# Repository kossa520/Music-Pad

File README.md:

# Music Pad Images:

## Preview:

## PCB Schemat:

## Case Schemat:

#  Project Requirements

## File List
* **PCB Design:**
  * `Music Pad.kicad_pcb`
  * `Music Pad.kicad_sch`
  * `Music Pad.kicad_pro`
* **Case Design:**
  * `Bottom.step`
  * `Top.step`
* **Keyboard Layout Styles:**
  * `keyboard-layout.json`
  * `plate-2026-02-05T17_30_58.558Z.dxf`
* **Programs:**
  * `code.py`
  * `libraries`

---

## Part List
| Quantity | Item | Notes |
| :--- | :--- | :--- |
| 1 | 3D Printed Case | Includes Bottom and Top files |
| 4 | M3x5mx4mm Heatset Inserts | |
| 4 | M3x16mm Screws | |
| 1 | 0.91 inch OLED Display | 4-pin version |
| 3 | DSA Keycaps | |
| 1 | Seeed XIAO RP2040 | |
| 3 | MX-Style Switches | |
| 1 | EC11 Rotary Encoder | |

## Setup Guide

### 1. Install CircuitPython

Download CircuitPython for XIAO RP2040 from [circuitpython.org](https://circuitpython.org/board/seeeduino_xiao_rp2040/)
Double-press the reset button on your XIAO RP2040 to enter bootloader mode
A drive named RPI-RP2 will appear
Copy the downloaded .uf2 file to this drive
The board will restart and appear as CIRCUITPY

### 2. Install Required Libraries

Download the CircuitPython libraries
Copy these folders/files to the lib folder on your CIRCUITPY drive:

adafruit_hid/
adafruit_display_text/
adafruit_framebuf.mpy
adafruit_ssd1306.mpy

### 3. Upload Firmware

Copy the music_pad_firmware.py firmware to the root of your CIRCUITPY drive
The board will automatically restart
You should see "Music Pad" and "Loading..." on the OLED display

## 4. Install Spotify Sender

Download Spotify Sender from programs folder
Go to https://developer.spotify.com/dashboard and click create app
Insert whatever name and description you want and in redirect URLs paste this: http://127.0.0.1:8888/callback
Click Web API and check the terms box then save
You will get your Client ID and client Secret copy those to the Spotify sender porgram you have downloaded 
Run the Spotify sender it should open chrome tab authorize it.

## Problems

If you have access denied problem with spotify sender try closing all apps that are using serial port with your RP2040 (for example MU Editor)

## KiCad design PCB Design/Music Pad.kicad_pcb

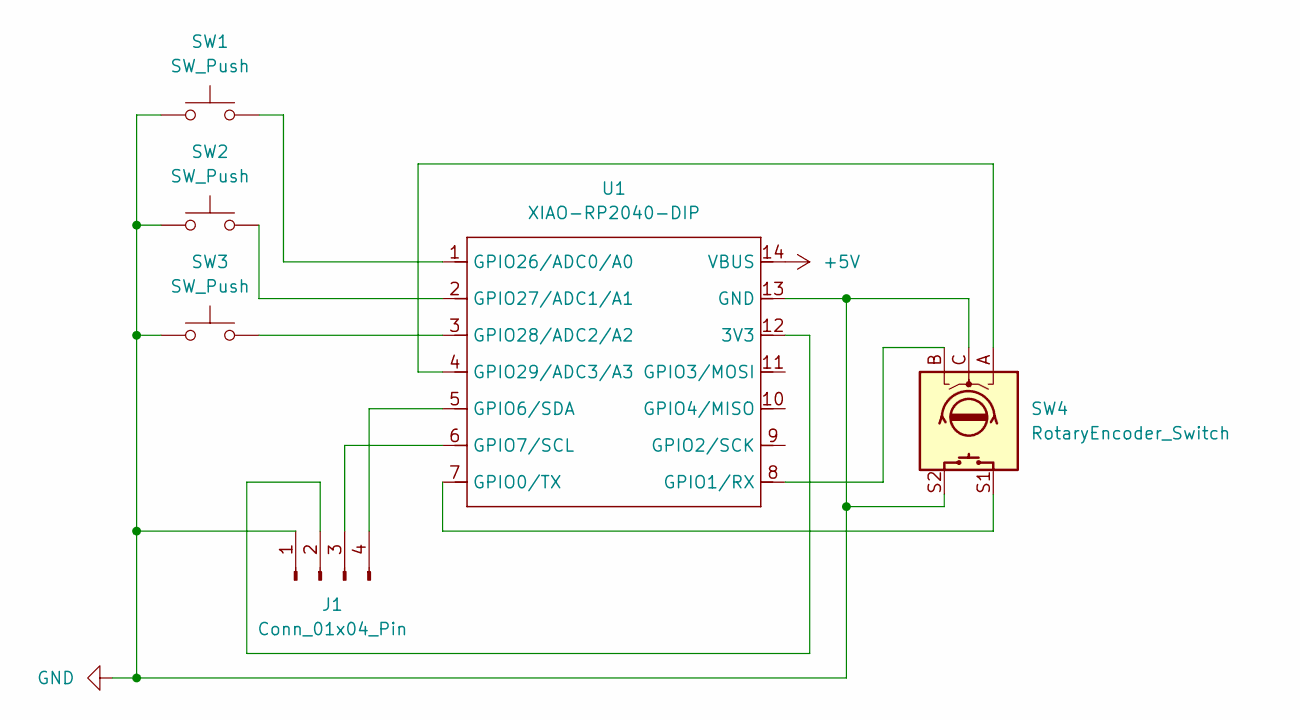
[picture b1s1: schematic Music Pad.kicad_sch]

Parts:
J1: Conn_01x04_Pin; SSD1306-0.91-OLED-4pin-128x32
SW1, SW2, SW3: SW_Push; SW_Cherry_MX_1.00u_PCB
SW4: RotaryEncoder_Switch; RotaryEncoder_Alps_EC11E-Switch_Vertical_H20mm
U1: XIAO-RP2040-DIP

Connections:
+5V: U1.14 (VBUS)
GND: J1.1, SW1.1, SW2.1, SW3.1, SW4.C, SW4.S2, U1.13 (GND)
unnamed: J1.2, U1.12 (3V3)
unnamed: J1.3, U1.6 (GPIO7/SCL)
unnamed: J1.4, U1.5 (GPIO6/SDA)
unnamed: SW4.S1, U1.7 (GPIO0/TX)
unnamed: SW4.B, U1.8 (GPIO1/RX)
unnamed: SW1.2, U1.1 (GPIO26/ADC0/A0)
unnamed: SW2.2, U1.2 (GPIO27/ADC1/A1)
unnamed: SW3.2, U1.3 (GPIO28/ADC2/A2)
unnamed: SW4.A, U1.4 (GPIO29/ADC3/A3)

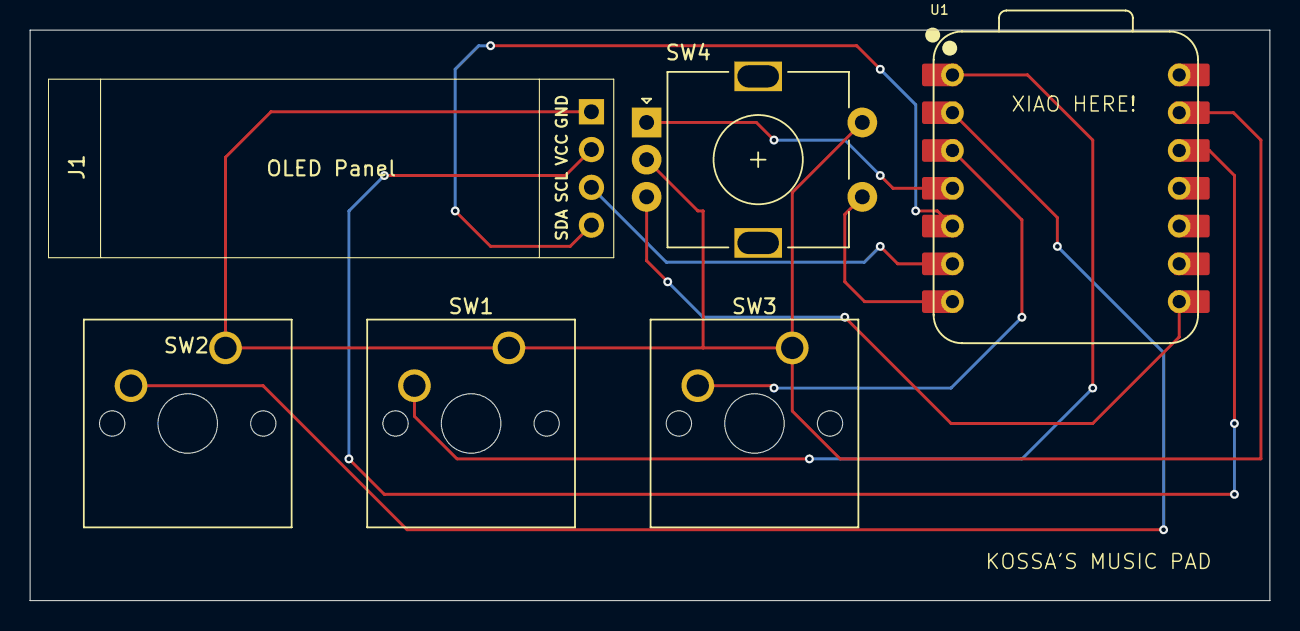
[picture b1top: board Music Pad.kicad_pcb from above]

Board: 2 copper layers, 83.3 x 38.3 mm, 6 parts (0 on the bottom side), 10 nets.

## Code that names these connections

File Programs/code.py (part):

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serial = usb_cdc.data

# Configure GPIO pins for switches
switch1_pin = board.D0  # GPIO26 - Play/Pause
switch2_pin = board.D1  # GPIO27 - Previous Track
switch3_pin = board.D2  # GPIO28 - Next Track

# Setup switches with pull-up resistors
switch1 = digitalio.DigitalInOut(switch1_pin)
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switch3.pull = digitalio.Pull.UP

# Setup rotary encoder with manual reading
encoder_a = digitalio.DigitalInOut(board.D3)  # GPIO29
encoder_a.direction = digitalio.Direction.INPUT
encoder_a.pull = digitalio.Pull.UP

encoder_b = digitalio.DigitalInOut(board.D7)  # GPIO1/RX
encoder_b.direction = digitalio.Direction.INPUT
encoder_b.pull = digitalio.Pull.UP

# Setup encoder button
encoder_btn_pin = board.D6  # GPIO0 - Encoder button
encoder_btn = digitalio.DigitalInOut(encoder_btn_pin)
encoder_btn.direction = digitalio.Direction.INPUT
encoder_btn.pull = digitalio.Pull.UP
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
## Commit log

2026-01-06 Update README.md
    added preview image
2026-01-06 added preview file
2026-01-06 Create folder
2026-01-06 moved file to folder
2026-01-06 Update and rename folderfile to a
2026-02-07 Create a
2026-02-18 Rename Spotify_sender.py to Spotify_sender.pyw
